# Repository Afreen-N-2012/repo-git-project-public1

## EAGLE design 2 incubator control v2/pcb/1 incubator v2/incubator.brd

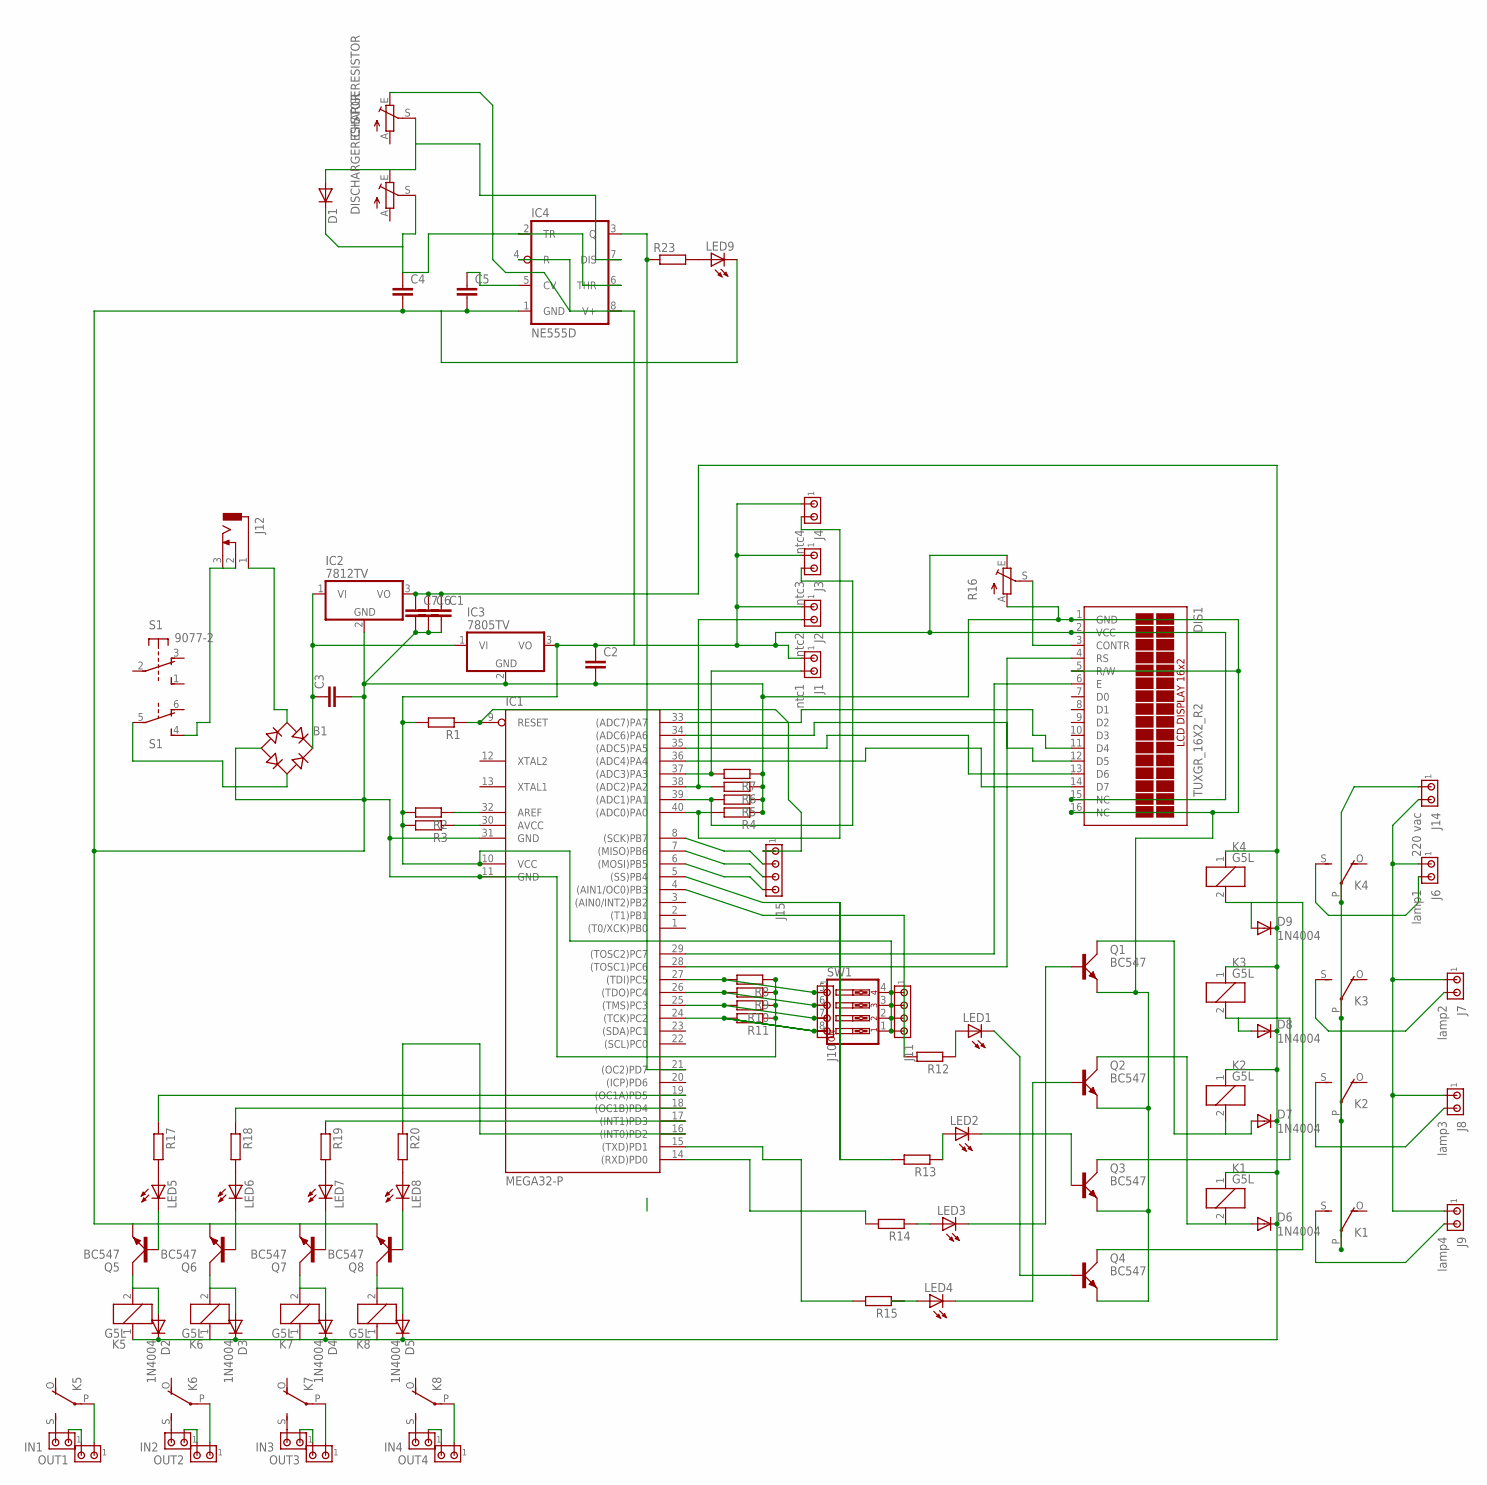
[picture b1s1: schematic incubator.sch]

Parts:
B1: RB1A
C1, C2, C3, C4, C6, C7: C5/2.5; C5B2.5
C5: C2,5-3; C2.5-3
CHARGERESISTOR: TRIM_EU-B64Y; B64Y
D1: DIODE-DO-214AC; DO-214AC
D2, D3, D4, D5, D6, D7, D8, D9: 1N4004; DO41-10
DIS1: TUXGR_16X2_R2
DISCHARGERESISTOR: TRIM_EU-B64Y; B64Y
IC1: MEGA32-P; DIL40
IC2: 7812TV; TO220V
IC3: 7805TV; TO220V
IC4: NE555D; SO08
IN1, IN2, IN3, IN4: MTA02-156; 1X2MTA
J1: ntc1; 1X2MTA
J2: ntc2; 1X2MTA
J3: ntc3; 1X2MTA
J4: ntc4; 1X2MTA
J6: lamp1; 1X2MTA
J7: lamp2; 1X2MTA
J8: lamp3; 1X2MTA
J9: lamp4; 1X2MTA
J10, J11, J15: MTA04-100; 10X04MTA
J12: DCJ0303
J14: 220 vac; 1X2MTA
K1, K2, K3, K4, K5, K6, K7, K8: G5L; G5LE
LED1, LED2, LED3, LED4, LED5, LED6, LED7, LED8, LED9: LED3MM
OUT1, OUT2, OUT3, OUT4: MTA02-156; 1X2MTA
Q1, Q2, Q3, Q4, Q5, Q6, Q7, Q8: BC547; SOT54A
R1, R2, R3, R4, R5, R6, R7, R8, R9, R10, R11, R12, R13, R14, R15, R17, R18, R19, R20, R23: RR1206; R1206
R16: TRIM_EU-B64Y; B64Y
S1: 9077-2
SW1: SW_DIP-4; EDG-04

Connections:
5V: C2.1, CHARGERESISTOR.E, DIS1.2 (VCC), DIS1.15 (NC), IC1.10 (VCC), IC3.3 (VO), IC4.4 (R), IC4.8 (V+), J1.1, J2.1, J3.1, J4.1, J11.1, J11.2, J11.3, J11.4, R1.2, R2.2, R3.2, R16.E, SW1.1, SW1.2, SW1.3, SW1.4
12V: C1.1, C6.1, C7.1, D2.C, D3.C, D4.C, D5.C, D6.C, D7.C, D8.C, D9.C, IC2.3 (VO), K1.1, K2.1, K3.1, K4.1, K5.1, K6.1, K7.1, K8.1
AREF: IC1.32 (AREF), R2.1
AVCC: IC1.30 (AVCC), R3.1
D4: DIS1.11 (D4), IC1.33 ((ADC7)PA7)
D5: DIS1.12 (D5), IC1.34 ((ADC6)PA6)
D6: DIS1.13 (D6), IC1.35 ((ADC5)PA5)
D7: DIS1.14 (D7), IC1.36 ((ADC4)PA4)
ENABLE: DIS1.6 (E), IC1.29 ((TOSC2)PC7)
GND: B1.-, C1.2, C2.2, C3.2, C4.2, C5.2, C6.2, C7.2, DIS1.1 (GND), DIS1.5 (R/W), DIS1.16 (NC), IC1.11 (GND), IC1.31 (GND), IC2.2 (GND), IC3.2 (GND), IC4.1 (GND), LED9.K (C), Q1.E, Q2.E, Q3.E, Q4.E, Q5.E, Q6.E, Q7.E, Q8.E, R4.1, R5.1, R6.1, R7.1, R8.1, R9.1, R10.1, R11.1, R16.A
MISO: IC1.7 ((MISO)PB6), J15.3
MOSI: IC1.6 ((MOSI)PB5), J15.4
unnamed: LED5.A, R17.2
unnamed: LED6.A, R18.2
unnamed: LED7.A, R19.2
unnamed: DIS1.3 (CONTR), R16.S
unnamed: LED8.A, R20.2
unnamed: LED5.K (C), Q5.B
unnamed: LED6.K (C), Q6.B
unnamed: LED7.K (C), Q7.B
unnamed: LED8.K (C), Q8.B
unnamed: J6.2, K4.S
unnamed: J7.2, K3.S
unnamed: J8.2, K2.S
unnamed: J9.2, K1.S
unnamed: IN1.2, K5.S
unnamed: J6.1, J7.1, J8.1, J9.1, J14.2
unnamed: J14.1, K1.P, K2.P, K3.P, K4.P
unnamed: D2.A, K5.2, Q5.C
unnamed: J12.2, J12.3, S1.4 (S)
unnamed: B1.AC1, J12.1
unnamed: B1.AC2, S1.5
unnamed: IC1.21 ((OC2)PD7), IC4.3 (Q), R23.1
unnamed: D3.A, K6.2, Q6.C
unnamed: D4.A, K7.2, Q7.C
unnamed: D5.A, K8.2, Q8.C
unnamed: IN1.1, OUT1.2
unnamed: IC1.15 ((TXD)PD1), R15.2
unnamed: IC1.14 ((RXD)PD0), R14.2
unnamed: LED4.K (C), Q2.B
unnamed: LED3.K (C), Q1.B
unnamed: IC1.5 ((SS)PB4), R13.2
unnamed: IC1.4 ((AIN1/OC0)PB3), R12.2
unnamed: IN2.1, OUT2.2
unnamed: IN3.1, OUT3.2
unnamed: IN4.1, OUT4.2
unnamed: LED1.K (C), Q4.B
unnamed: LED2.K (C), Q3.B
unnamed: D6.A, K1.2, Q2.C
unnamed: D7.A, K2.2, Q1.C
unnamed: D8.A, K3.2, Q3.C
unnamed: D9.A, K4.2, Q4.C
unnamed: IN2.2, K6.S
unnamed: IN3.2, K7.S
unnamed: IN4.2, K8.S
unnamed: K5.P, OUT1.1
unnamed: K6.P, OUT2.1
unnamed: K7.P, OUT3.1
unnamed: K8.P, OUT4.1
unnamed: IC1.16 ((INT0)PD2), R20.1
unnamed: IC1.17 ((INT1)PD3), R19.1
unnamed: IC1.18 ((OC1B)PD4), R18.1
unnamed: IC1.19 ((OC1A)PD5), R17.1
unnamed: C5.1, IC4.5 (CV)
unnamed: C4.1, D1.C, DISCHARGERESISTOR.S, IC4.2 (TR), IC4.6 (THR)
unnamed: LED9.A, R23.2
unnamed: LED1.A, R12.1
unnamed: LED2.A, R13.1
unnamed: LED4.A, R15.1
unnamed: LED3.A, R14.1
unnamed: CHARGERESISTOR.S, D1.A, DISCHARGERESISTOR.E, IC4.7 (DIS)
NTC1: IC1.37 ((ADC3)PA3), J1.2, R7.2
NTC2: IC1.38 ((ADC2)PA2), J2.2, R6.2
NTC3: IC1.39 ((ADC1)PA1), J3.2, R5.2
NTC4: IC1.40 ((ADC0)PA0), J4.2, R4.2
RS: DIS1.4 (RS), IC1.28 ((TOSC1)PC6)
RST: IC1.9 (RESET), J15.1, R1.1
SCK: IC1.8 ((SCK)PB7), J15.2
SW1: IC1.27 ((TDI)PC5), J10.1, R8.2, SW1.5
SW2: IC1.26 ((TDO)PC4), J10.2, R9.2, SW1.6
SW3: IC1.25 ((TMS)PC3), J10.3, R10.2, SW1.7
SW4: IC1.24 ((TCK)PC2), J10.4, R11.2, SW1.8
VIN: B1.+, C3.1, IC2.1 (VI), IC3.1 (VI)

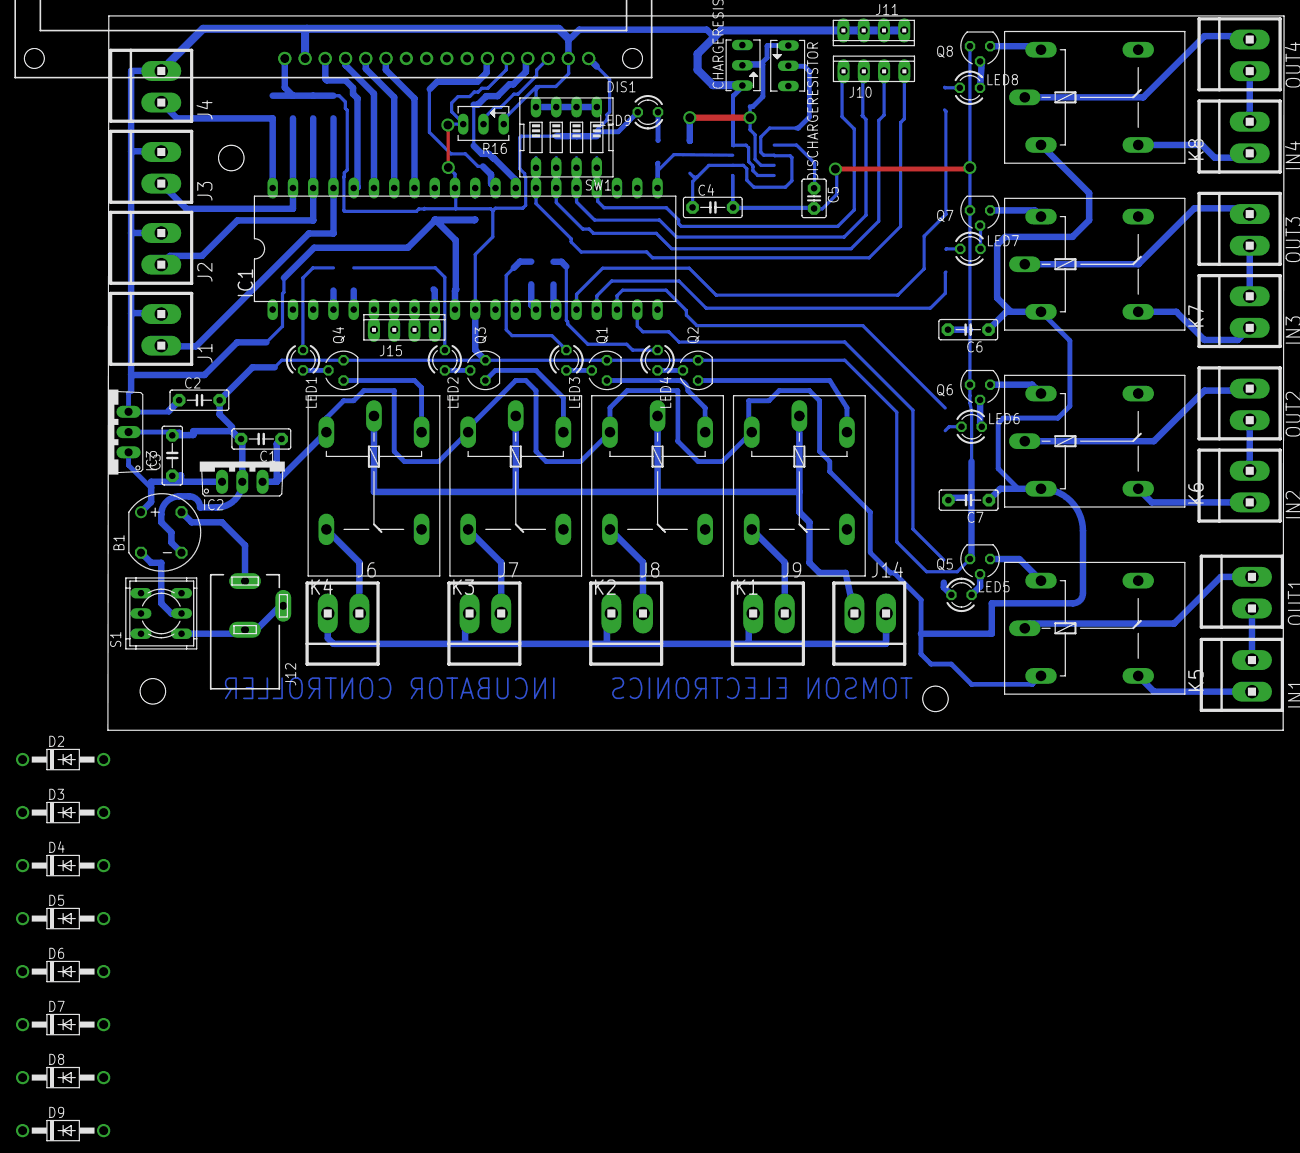
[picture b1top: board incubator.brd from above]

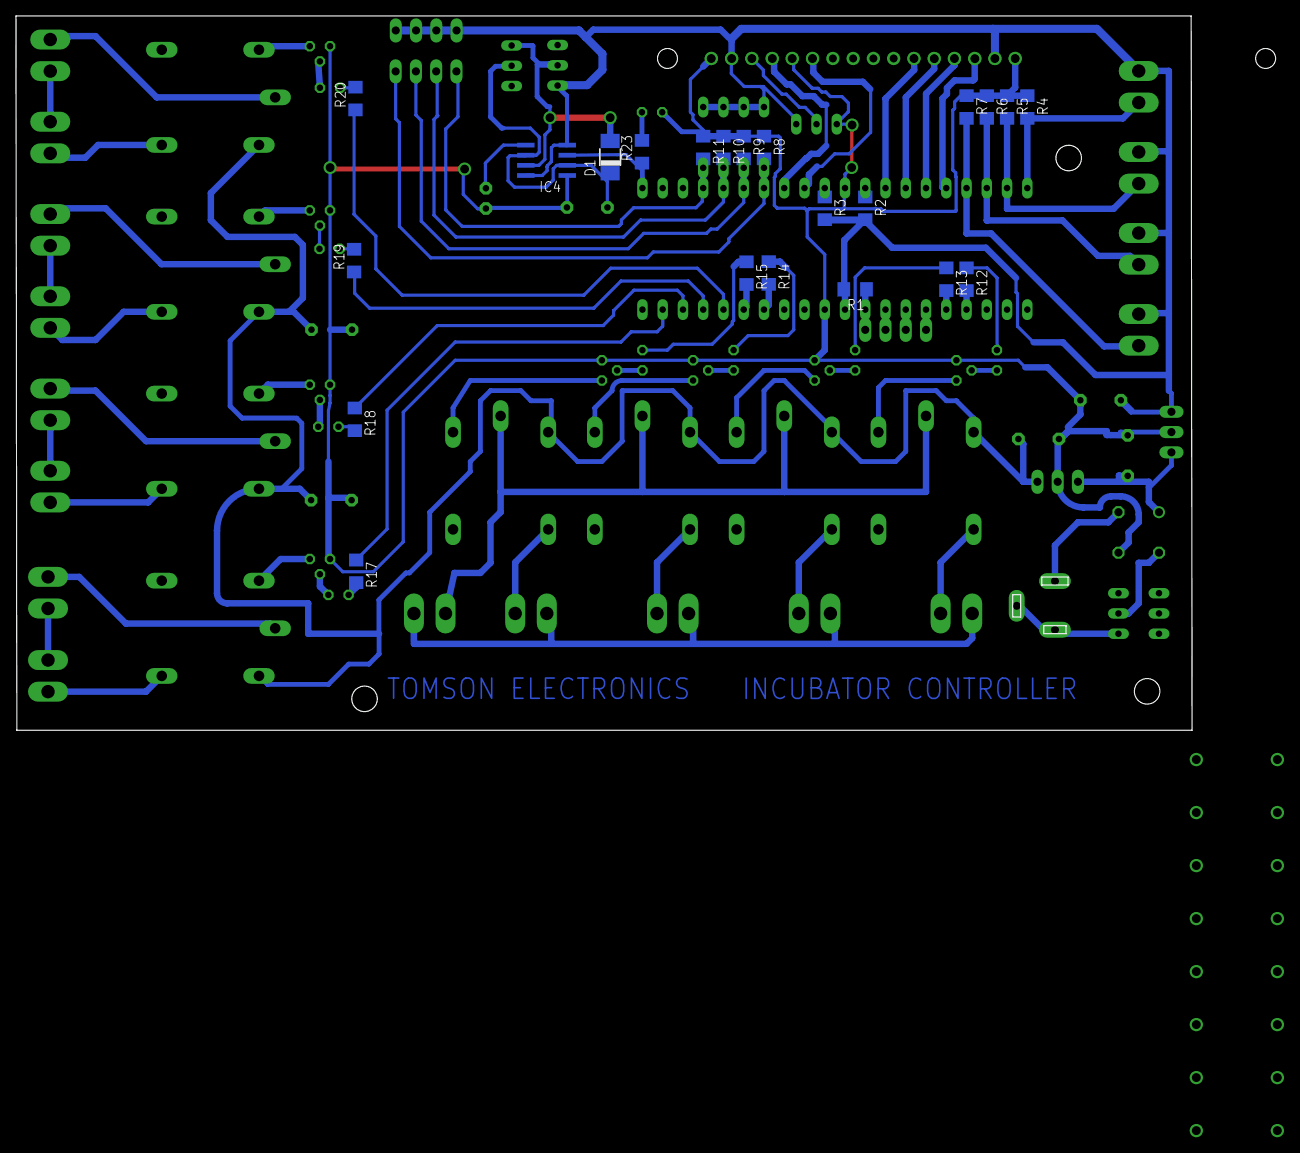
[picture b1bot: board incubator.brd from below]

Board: 2 copper layers, 147.5 x 89.6 mm, 93 parts (22 on the bottom side), 83 nets.

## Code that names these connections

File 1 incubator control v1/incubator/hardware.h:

#define htemp 100
#define ltemp 97
#define ntc1 3
#define ntc2 2
#define ntc3 1
#define ntc4 0
#define sw1 29
#define sw2 28
#define sw3 27
#define sw4 26
#define lamp1 11
#define lamp2 12
#define lamp3 24
#define lamp4 25
#define mot1a 22
#define mot1b 21
#define mot2a 20
#define mot2b 19
#define mot3a 18
#define mot3b 23
#define mot4a 16
#define mot4b 17
#define rs 30
#define en 31
#define d4 0
#define d5 1
#define d6 2
#define d7 3

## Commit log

2015-10-13 push all files to repo
